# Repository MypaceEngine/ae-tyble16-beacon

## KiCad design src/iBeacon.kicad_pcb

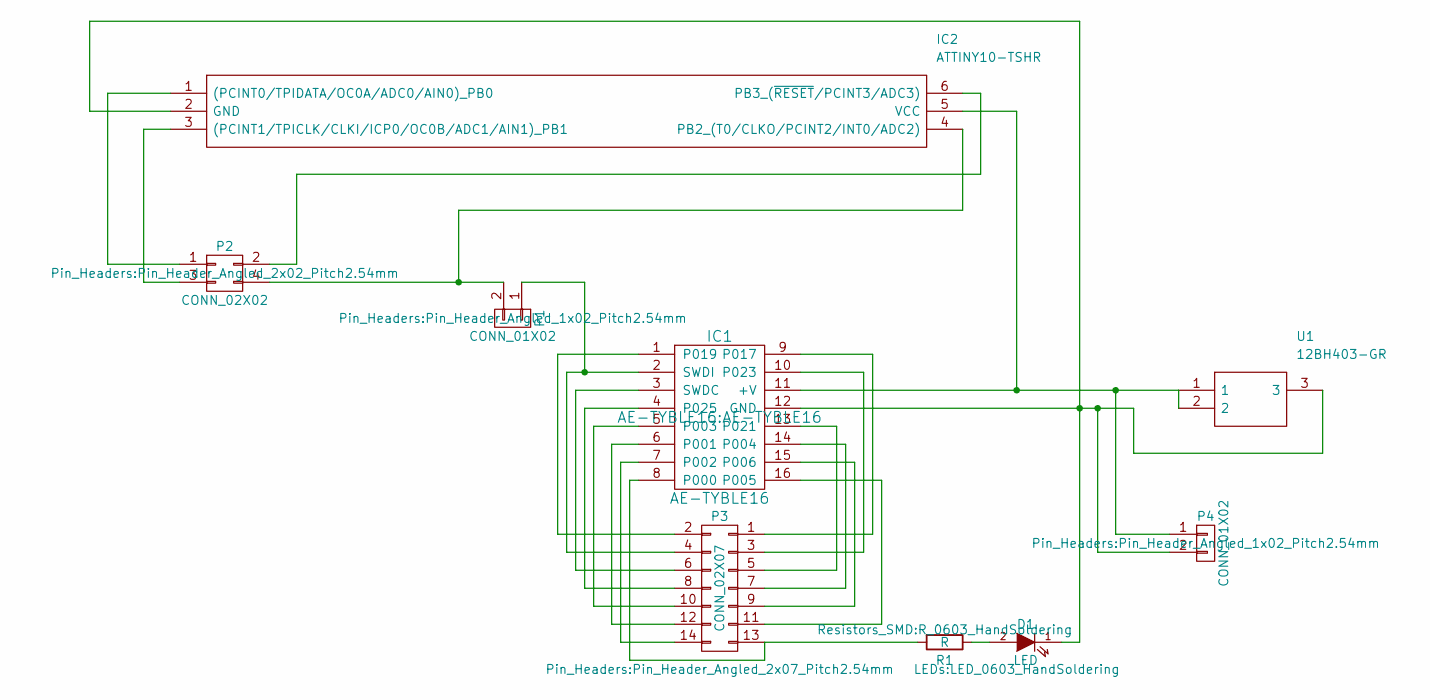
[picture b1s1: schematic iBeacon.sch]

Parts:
D1: LED; LED_0603_HandSoldering
IC1: AE-TYBLE16
IC2: ATTINY10-TSHR; SOT95P280X145-6N; Manufacturer_Part_Number ATTINY10-TSHR; Mouser Part Number 556-ATTINY10-TSHR
P1, P4: CONN_01X02; Pin_Header_Angled_1x02_Pitch2.54mm
P2: CONN_02X02; Pin_Header_Angled_2x02_Pitch2.54mm
P3: CONN_02X07; Pin_Header_Angled_2x07_Pitch2.54mm
R1: R; R_0603_HandSoldering
U1: 12BH403-GR; 12BH403GR; Manufacturer_Part_Number 12BH403-GR; Mouser Part Number 12BH403-GR

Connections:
unnamed: D1.1 (K), IC1.12 (GND), IC2.2 (GND), P4.2, U1.3
unnamed: D1.2 (A), R1.1
unnamed: IC1.1 (P019), P3.2
unnamed: IC1.2 (SWDI), P1.1, P3.4
unnamed: IC1.3 (SWDC), P3.6
unnamed: IC1.4 (P025), P3.8
unnamed: IC1.5 (P003), P3.10
unnamed: IC1.6 (P001), P3.12
unnamed: IC1.7 (P002), P3.14
unnamed: IC1.8 (P000), P3.13, R1.2
unnamed: IC1.9 (P017), P3.1
unnamed: IC1.10 (P023), P3.3
unnamed: IC1.11 (+V), IC2.5 (VCC), P4.1, U1.1, U1.2
unnamed: IC1.13 (P021), P3.5
unnamed: IC1.14 (P004), P3.7
unnamed: IC1.15 (P006), P3.9
unnamed: IC1.16 (P005), P3.11
unnamed: IC2.1 ((PCINT0/TPIDATA/OC0A/ADC0/AIN0)_PB0), P2.1
unnamed: IC2.3 ((PCINT1/TPICLK/CLKI/ICP0/OC0B/ADC1/AIN1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), P2.3
unnamed: IC2.4 (PB2_(T0/CLKO/PCINT2/INT0/ADC2)), P1.2, P2.4
unnamed: IC2.6 (PB3_(~RESET~/PCINT3/ADC3)), P2.2

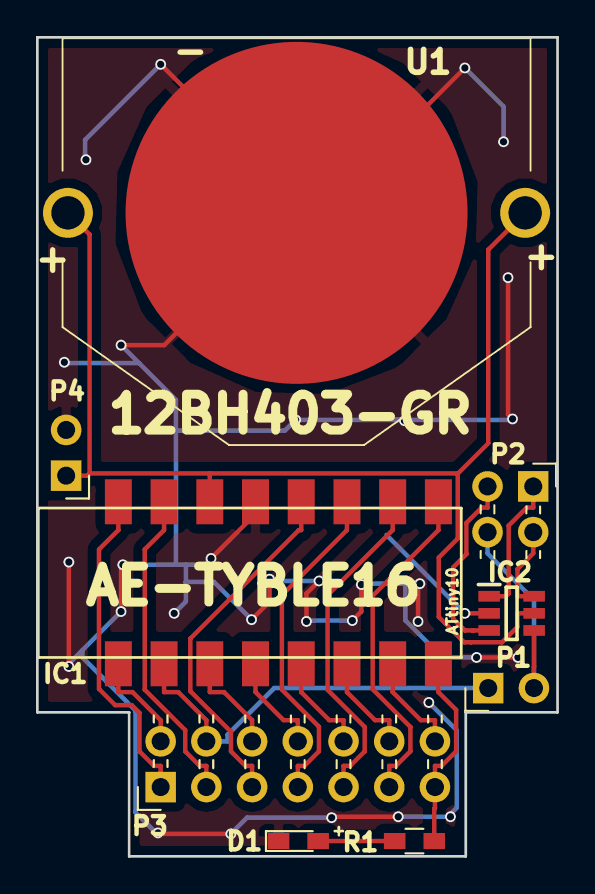
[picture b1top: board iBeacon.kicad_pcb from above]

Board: 2 copper layers, 28.9 x 45.5 mm, 9 parts (0 on the bottom side), 21 nets.

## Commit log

2019-03-06 Add gerber/iBeacon-B.Adhes.gbr Add gerber/iBeacon-B.CrtYd.gbr Add gerber/iBeacon-B.Cu.gbr Add gerber/iBeacon-B.Fab.gbr Add gerber/iBeacon-B.Mask.gbr Add gerber/iBeacon-B.Paste.gbr Add gerber/iBeacon-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
2019-04-05 2nd Version
2019-04-12 Redesigning board
